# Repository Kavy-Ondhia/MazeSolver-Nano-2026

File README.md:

<h1 align="center">MazeSolver-Nano-2026 🏎️💨</h1>

A high-performance line-following and maze-solving robot built on the Arduino Nano platform. This project utilizes PID control and magnetic encoders for precision navigation.

<div align="center">
  <table style="width:100%; border-collapse: collapse; border: none; table-layout: fixed;">
    <tr>
      <td rowspan="2" style="width: 60%; border: none; padding: 2px;">
        
      </td>
      <td style="width: 40%; border: none; padding: 2px;">
        
      </td>
    </tr>
    <tr>
      <td style="border: none; padding: 2px;">
        
      </td>
    </tr>
  </table>
</div>

## 🛠 Prototyping & PCB Manufacturing Phase
The project has moved from theoretical design to **active hardware-in-the-loop (HIL) testing**. I am currently validating a breadboard prototype to finalize signal routing and power stability for the custom PCB fabrication.

### **Current Progress:**
* **Prototype Controller:** Arduino Nano (ATmega328P) using a logic-stable common ground architecture.
* **Dual Motor Drive:** Integrated the **DRV8833 Dual H-Bridge** for the prototype phase, utilizing PWM-direct control to manage motor velocity and direction.
* **Sensor Integration:** Successfully calibrated a **QTR-8RC 8-channel array**. Pin mapping has been optimized (A0–A5, D7, D13) to prevent conflicts with motor PWM timers.
* **Precise Navigation:** Magnetic encoders are mapped to **Hardware Interrupt pins (D2, D3)** to ensure zero-loss pulse counting for PID speed control and distance tracking.

### **PCB Design Priorities:**
* **Signal Integrity:** Separating high-current motor traces from sensitive Encoder and Sensor signal lines to reduce Electromagnetic Interference (EMI).
* **Power Rail Optimization:** Implementing a **Buck Converter** to efficiently step down LiPo battery voltage for the logic circuit, significantly reducing heat compared to linear regulators.
* **Modular Footprint:** The PCB layout is being designed with a modular header to support both **DRV8833** and **TB6612FNG** driver footprints for testing flexibility.

## 👥 Development Team
* **Kavy Ondhia** ([@Kavy-Ondhia](https://github.com/Kavy-Ondhia))  
  *Lead Engineer — Firmware Architecture, Logic, & Hardware V2 (KiCad)*
  
* **Karunya Jajoo** ([@karunya-jajoo](https://github.com/karunya-jajoo))  
  *Contributor — Initial Hardware Concept & V1 Schematic*

## 🛠 Hardware Specifications

| Component | Purpose | Datasheet/Reference |
| :--- | :--- | :--- |
| **Arduino Nano** | Main Controller | [Official Manual](https://docs.arduino.cc/resources/datasheets/A000005-datasheet.pdf) |
| **TB6612FNG** | Motor Driver | [Toshiba Datasheet](https://www.sparkfun.com/datasheets/Robotics/TB6612FNG.pdf) |
| **N20 Motors** | 6V 200RPM w/ Encoders | [Technical Specs](https://www.handsontec.com/dataspecs/motor/N20-Motor.pdf) |
| **QTR-8RC** | IR Sensor Array | [Pololu Documentation](https://www.pololu.com/docs/0J12) |
| **SSD1306 OLED** | Debugging Display | [Adafruit Datasheet](https://cdn-shop.adafruit.com/datasheets/SSD1306.pdf) |
| **HC-05** | Bluetooth Module | [HC-05 Datasheet](https://components101.com/sites/default/files/component_datasheet/HC-05-Datasheet.pdf) |
| **LM2596 Buck** | 5V Regulation | [TI Datasheet](https://www.ti.com/lit/ds/symlink/lm2596.pdf) |

## 🔌 Proposed Pin Mapping (Nano)
*This table serves as the "contract" for the schematic design.*

| Standard Pin | KiCad Symbol Label | Component | Function | Status vs. Old |
| :--- | :--- | :--- | :--- | :--- |
| **D2** | D2 (Right Pin 11) | Encoder Left | Interrupt A (Phase A) | UNCHANGED |
| **D11** | D11 (Right Pin 2) | Encoder Left | Phase B (Dir Tracking) | UNCHANGED |
| **D3** | D3 (Right Pin 10) | Encoder Right | Interrupt B (Phase A) | UNCHANGED |
| **D12** | D12 (Right Pin 1) | Encoder Right | Phase B (Dir Tracking) | UNCHANGED |
| **D4** | D4 (Right Pin 9) | TB6612 (BIN1) | Right Motor Dir | UNCHANGED |
| **D5** | D5 (Right Pin 8) | TB6612 (BIN2) | Right Motor Dir | UNCHANGED |
| **D7** | D7 (Right Pin 6) | TB6612 (AIN1) | Left Motor Dir | UNCHANGED |
| **D8** | D8 (Right Pin 5) | TB6612 (AIN2) | Left Motor Dir | UNCHANGED |
| **D9** | D9 (Right Pin 4) | TB6612 (PWMA) | Left Motor Speed (PWM) | UNCHANGED |
| **D10** | D10 (Right Pin 3) | TB6612 (PWMB) | Right Motor Speed (PWM) | UNCHANGED |
| **A0** | D14 (Left Pin 4) | QTR-8RC Pin 1 | IR Reflectance | UNCHANGED |
| **A1** | D15 (Left Pin 5) | QTR-8RC Pin 2 | IR Reflectance | UNCHANGED |
| **A2** | D16 (Left Pin 6) | QTR-8RC Pin 3 | IR Reflectance | UNCHANGED |
| **A3** | D17 (Left Pin 7) | QTR-8RC Pin 4 | IR Reflectance | UNCHANGED |
| **D6** | D6 (Right Pin 7) | QTR-8RC Pin 5 | IR Reflectance | UNCHANGED |
| **A4** | D18 (Left Pin 8) | QTR-8RC Pin 6 | IR Reflectance | **MOVED** (From D13) |
| **A5** | D19 (Left Pin 9) | QTR-8RC Pin 7 | IR Reflectance | **MOVED** (From A6) |
| **D13** | D13 (Left Pin 1) | QTR-8RC Pin 8 | IR Reflectance | **MOVED** (From A7) |
| **D0** | D0 (RX) | NOT USED | Leave Empty for Uploads | **REMOVED** (Finish LED) |
| **A6 / A7** | A6 / A7 | NOT USED | Hardware Input Only | **VOID** |

### ⚠️ Critical Hardware Notes
* **A6/A7 Pins:** These pins on the Nano are **Analog Input Only**. They cannot be used for the QTR-8RC or Motor Standby because they cannot function as Digital Outputs.
* **QTR-8RC Version:** This project uses the **RC (Digital)** version of the sensor. Pins are toggled as outputs to charge the onboard capacitor, then read as inputs to measure discharge time.
* **USB Uploading:** Digital Pin **D0 (RX)** is left disconnected to prevent serial communication conflicts during code uploading.

## 🛠 Hardware Design

[Download PDF Version](hardware/schematic_v2/Schematic_pdf/Schematic_v2.1.pdf)

## 🧠 Software Logic & Path Optimization

The robot's intelligence is divided into three layers: **Perception**, **Control**, and **Strategy**.

### 1. Perception & Control (PID)
* **The Error:** Using the QTR-8RC, we calculate the robot's position relative to the center (3500). 
    * $Error = 3500 - \text{Current Reading}$
* **PID Math:** We use Proportional (Muscle) and Derivative (Brakes) logic to calculate correction.
    * `Correction = (Kp * error) + (Kd * (error - lastError))`
    * `LeftSpeed = Base + Correction` | `RightSpeed = Base - Correction`

### 2. The Discovery Phase (Dry Run)
The robot uses a **Preferential Wall-Following Rule** (Straight > Left > Right). 
* **The Log:** Every move is recorded in a memory array.
* **Encoder Mapping:** Encoders track distance in millimeters to ensure precise turns and junction detection.

### 3. Path Optimization (The "Aha!" Moment)
The robot simplifies its recorded path by removing dead ends (represented as 'B' for Back).
* **Logic:** `Left -> Back -> Left` is simplified to `Straight`.
* **Optimization Example:** `L -> B -> L` becomes `S`. This "shrinks" the journey for the final run.

### 4. Advanced Mapping & Exploration
To cover the entire map, the robot utilizes a coordinate-based Node system:
```cpp
struct Node {
  long x;           // X coordinate from encoders
  long y;           // Y coordinate from encoders
  bool visited[3];  // [Left, Straight, Right]
  int parentNode;   // Back-tracking reference
};
```

## 📸 Component Gallery

## 📂 Project Structure
* `/src`: Final Arduino (.ino) and configuration (.h) files.
* `/hardware`: Schematic diagrams and PCB layouts (In Progress).
* `/media`: Component photos and project progress shots.

---
*Created by [Kavy Ondhia](https://github.com/Kavy-Ondhia)*

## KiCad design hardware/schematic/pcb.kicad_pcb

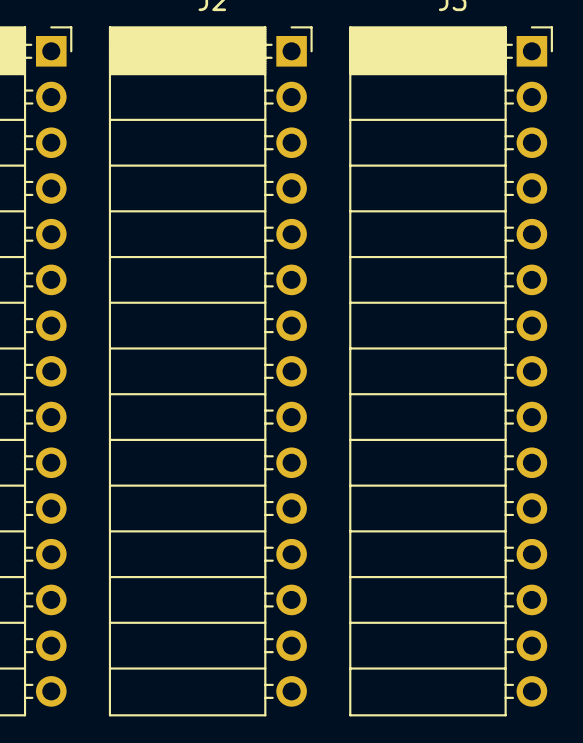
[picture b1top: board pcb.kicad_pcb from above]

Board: 2 copper layers, 3 parts (0 on the bottom side), 10 nets, no tracks yet.

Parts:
J1: L; PinSocket_1x15_P2.54mm_Horizontal
J2: R; PinSocket_1x15_P2.54mm_Horizontal
J3: IR; PinSocket_1x15_P2.54mm_Horizontal

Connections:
unnamed: J1.12 (5V), J3.11 (VCC)
unnamed: J1.10 (A6), J3.10 (D8)
unnamed: J2.11 (D2), J3.3 (D1)
unnamed: J2.9 (D4), J3.4 (D2)
unnamed: J2.6 (D7), J3.5 (D3)
unnamed: J2.5 (D8), J3.6 (D4)
unnamed: J2.3 (D10), J3.7 (D5)
unnamed: J2.2 (D11), J3.8 (D6)
unnamed: J2.1 (D12), J3.9 (D7)
unnamed: J2.12 (GND), J3.1 (GND)

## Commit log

2026-01-08 Add .gitignore for Arduino and build files
2026-01-08 Add MIT License to the project
2026-01-08 docs: Initial project structure and hardware spec sheet
2026-01-09 feat: setup motor pins and QTR calibration logic
2026-01-09 chore: critical fix for file content swap
2026-01-09 docs: fix broken links and add pin mapping table
2026-01-09 docs: add high-quality photos of hardware components
2026-01-09 docs: fix table formatting and embed gallery images
2026-01-09 docs: add path optimization and PID logic
2026-01-09 feat: initial KiCad project setup with Nano symbol
2026-01-09 feat: add initial hardware files
2026-01-10 docs: update pin mapping table to match KiCad labels
2026-01-10 Update: Finalized pin map to support 8 sensors + OLED by moving QTR pins to D0/D1
2026-01-10 Update: Fixed Pin Mapping
2026-01-11 Update pin mapping: Moved IR sensors to free up I2C for OLED
2026-01-11 Hardware: Full schematic overhaul
2026-01-11 Hardware: Schematic added
2026-01-11 Update: Readme file minor changes
2026-01-11 Fixed readme file
2026-01-12 Hardware: Minor changes in schematic
2026-01-12 Hardware: Changed readme file and added schematic pdf and photo
2026-01-13 Hardware: Minor schematic changes
2026-01-13 Fix: Remap pins to resolve A6/A7 and RX/TX conflicts
2026-01-13 Software: Changed files according to new pin mapping
2026-01-13 Minor changes in readme file
2026-01-13 Minor change in readme file
2026-01-14 Software: Implemented sensor logic
2026-01-14 Added images of Arduino Nano
2026-01-15 Hardware: Changed schematic according to new pin mapping
2026-01-15 Minor changes
2026-01-15 Minor change
2026-01-16 Added prototype images
2026-01-16 refactor: initialize Hardware V2 and update project ownership
    - Migrated hardware design to KiCad for V2 schematic.
    - Assumed lead for Hardware Design & PCB Layout.
    - Updated README to reflect current development team roles.
2026-01-16 Added new v2.1 schematic
